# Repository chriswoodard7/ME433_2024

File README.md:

# ME433_2024
Repo for ME 433 assignments during the Spring 2024 quarter

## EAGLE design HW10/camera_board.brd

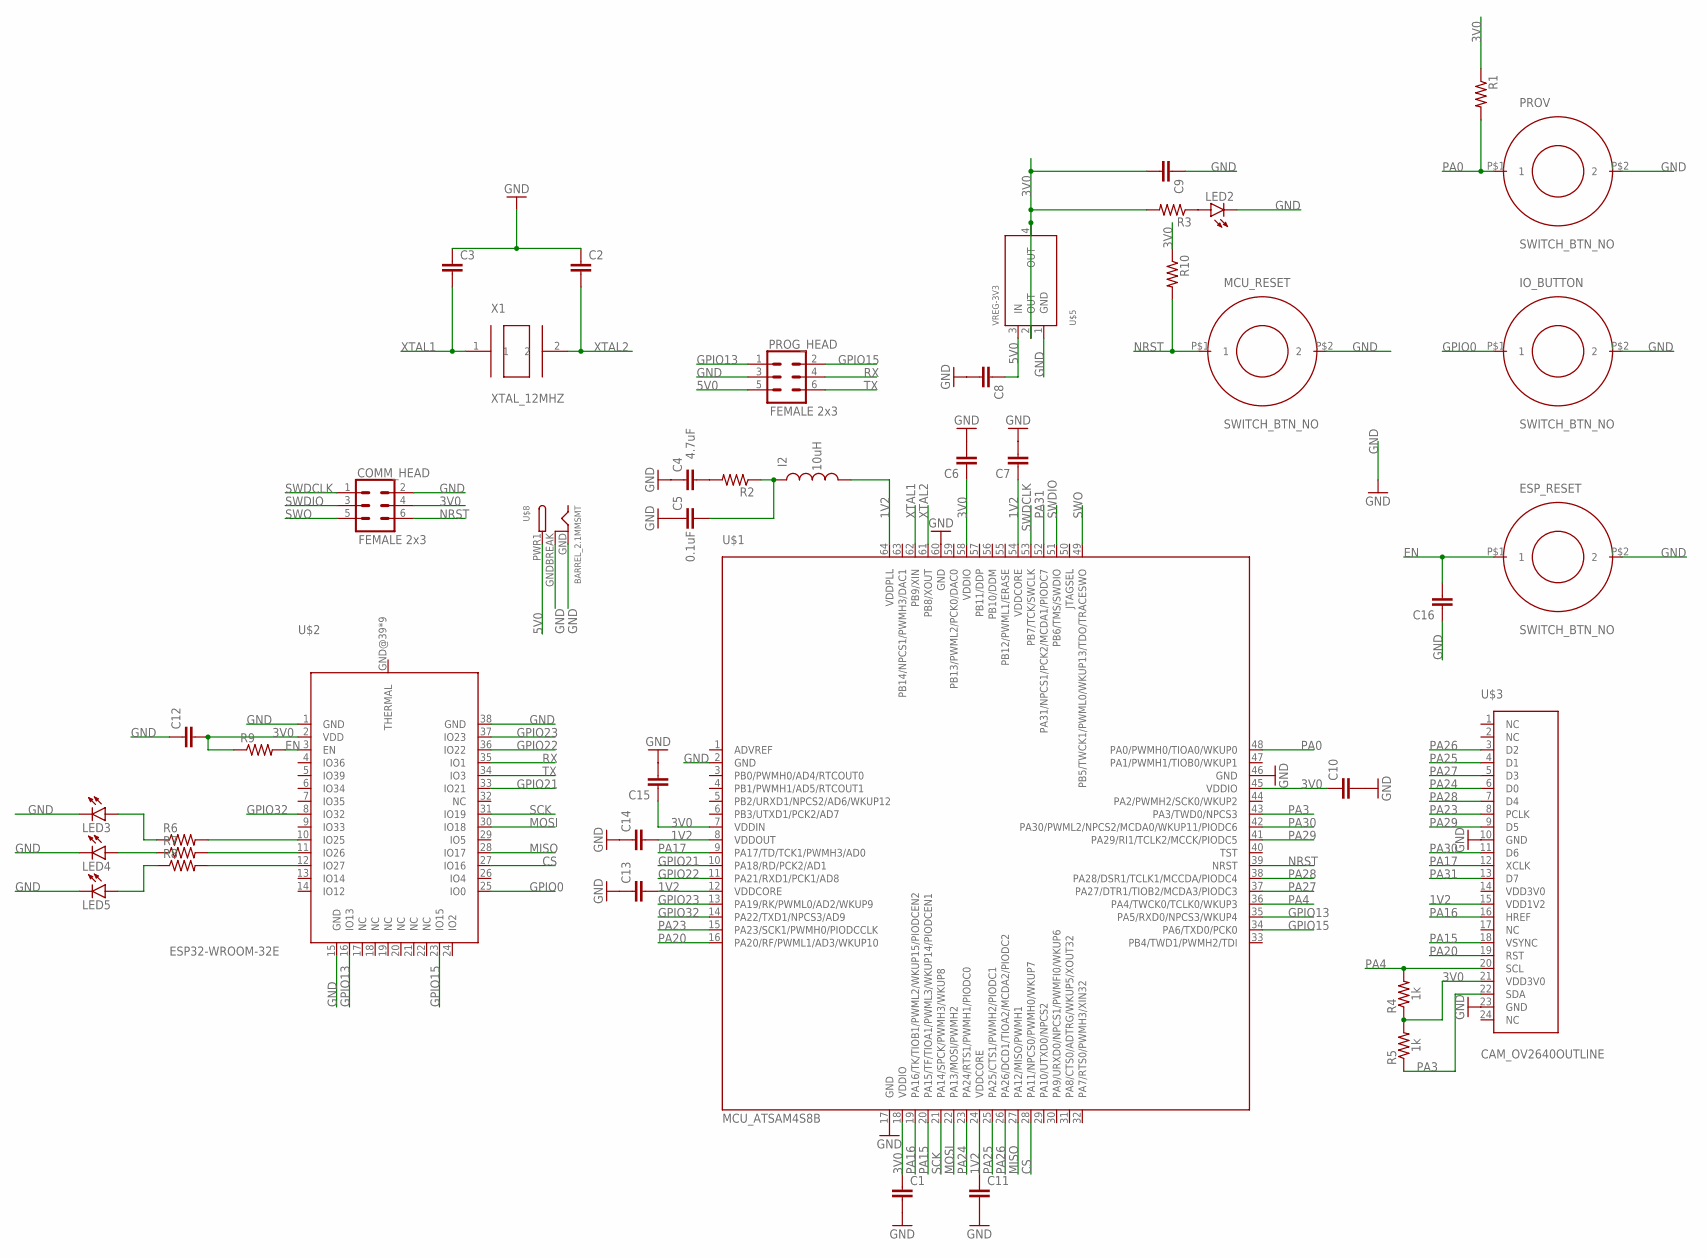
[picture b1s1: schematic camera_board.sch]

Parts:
C1, C2, C3, C6, C7, C8, C9, C10, C11, C12, C13, C14, C15, C16: CAP; 0805
C4: 4.7uF; 0805
C5: 0.1uF; 0805
COMM_HEAD: FEMALE 2x3; 2X3
ESP_RESET: SWITCH_BTN_NO; BTN_2
I2: 10uH; 0805
IO_BUTTON: SWITCH_BTN_NO; BTN_2
LED2, LED3, LED4, LED5: LED0603; LED-0603
MCU_RESET: SWITCH_BTN_NO; BTN_2
PROG_HEAD: FEMALE 2x3; 2X3
PROV: SWITCH_BTN_NO; BTN_2
R1, R2, R3, R6, R7, R8, R9, R10: RES; 0805
R4, R5: 1k; 0805
U$1: MCU_ATSAM4S8B; QFP50P1200X1200X160-64N
U$2: ESP32-WROOM-32E
U$3: CAM_OV2640OUTLINE; CAM_CONN
U$5: VREG-3V3; R-PDSO-G4_TI
U$8: BARREL_2.1MMSMT; DCJACK_2MM_SMT
X1: XTAL_12MHZ; ABM7-16.000MHZ-D2Y-T

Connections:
1V2: C7.1, C11.1, C13.2, C14.2, I2.2, U$1.8 (VDDOUT), U$1.12 (VDDCORE), U$1.24 (VDDCORE), U$1.54 (VDDCORE), U$1.64 (VDDPLL), U$3.15 (VDD1V2)
3V0: C1.1, C6.1, C9.2, C10.1, C12.2, C15.1, COMM_HEAD.4, R1.1, R3.2, R4.1, R5.2, R9.1, R10.1, U$1.7 (VDDIN), U$1.18 (VDDIO), U$1.45 (VDDIO), U$1.58 (VDDIO), U$2.2 (VDD), U$3.21 (VDD3V0), U$5.2 (OUT), U$5.4 (OUT)
5V0: C8.1, PROG_HEAD.5, U$5.3 (IN), U$8.PWR1 (PWR)
CS: U$1.28 (PA11/NPCS0/PWMH0/WKUP7), U$2.27 (IO16)
EN: C16.2, ESP_RESET.P$1 (1), R9.2, U$2.3 (EN)
GND: C1.2, C2.1, C3.1, C4.1, C5.1, C6.2, C7.2, C8.2, C9.1, C10.2, C11.2, C12.1, C13.1, C14.1, C15.2, C16.1, COMM_HEAD.2, ESP_RESET.P$2 (2), IO_BUTTON.P$2 (2), LED2.C, LED3.C, LED4.C, LED5.C, MCU_RESET.P$2 (2), PROG_HEAD.3, PROV.P$2 (2), U$1.2 (GND), U$1.17 (GND), U$1.46 (GND), U$1.60 (GND), U$2.1 (GND), U$2.15 (GND), U$2.38 (GND), U$3.10 (GND), U$3.23 (GND), U$5.1 (GND), U$8.GND, U$8.GNDBREAK
GPIO0: IO_BUTTON.P$1 (1), U$2.25 (IO0)
GPIO13: PROG_HEAD.1, U$1.35 (PA5/RXD0/NPCS3/WKUP4), U$2.16 (IO13)
GPIO15: PROG_HEAD.2, U$1.34 (PA6/TXD0/PCK0), U$2.23 (IO15)
GPIO21: U$1.10 (PA18/RD/PCK2/AD1), U$2.33 (IO21)
GPIO22: U$1.11 (PA21/RXD1/PCK1/AD8), U$2.36 (IO22)
GPIO23: U$1.13 (PA19/RK/PWML0/AD2/WKUP9), U$2.37 (IO23)
GPIO32: U$1.14 (PA22/TXD1/NPCS3/AD9), U$2.8 (IO32)
MISO: U$1.27 (PA12/MISO/PWMH1), U$2.28 (IO17)
MOSI: U$1.22 (PA13/MOSI/PWMH2), U$2.30 (IO18)
unnamed: C5.2, I2.1, R2.1
unnamed: C4.2, R2.2
unnamed: LED2.A, R3.1
unnamed: LED3.A, R6.1
unnamed: R6.2, U$2.10 (IO25)
unnamed: R7.2, U$2.11 (IO26)
unnamed: R8.2, U$2.12 (IO27)
unnamed: LED4.A, R7.1
unnamed: LED5.A, R8.1
NRST: COMM_HEAD.6, MCU_RESET.P$1 (1), R10.2, U$1.39 (NRST)
PA0: PROV.P$1 (1), R1.2, U$1.48 (PA0/PWMH0/TIOA0/WKUP0)
PA3: R5.1, U$1.43 (PA3/TWD0/NPCS3), U$3.22 (SDA)
PA4: R4.2, U$1.36 (PA4/TWCK0/TCLK0/WKUP3), U$3.20 (SCL)
PA15: U$1.20 (PA15/TF/TIOA1/PWML3/WKUP14/PIODCEN1), U$3.18 (VSYNC)
PA16: U$1.19 (PA16/TK/TIOB1/PWML2/WKUP15/PIODCEN2), U$3.16 (HREF)
PA17: U$1.9 (PA17/TD/TCK1/PWMH3/AD0), U$3.12 (XCLK)
PA20: U$1.16 (PA20/RF/PWML1/AD3/WKUP10), U$3.19 (RST)
PA23: U$1.15 (PA23/SCK1/PWMH0/PIODCCLK), U$3.8 (PCLK)
PA24: U$1.23 (PA24/RTS1/PWMH1/PIODC0), U$3.6 (D0)
PA25: U$1.25 (PA25/CTS1/PWMH2/PIODC1), U$3.4 (D1)
PA26: U$1.26 (PA26/DCD1/TIOA2/MCDA2/PIODC2), U$3.3 (D2)
PA27: U$1.37 (PA27/DTR1/TIOB2/MCDA3/PIODC3), U$3.5 (D3)
PA28: U$1.38 (PA28/DSR1/TCLK1/MCCDA/PIODC4), U$3.7 (D4)
PA29: U$1.41 (PA29/RI1/TCLK2/MCCK/PIODC5), U$3.9 (D5)
PA30: U$1.42 (PA30/PWML2/NPCS2/MCDA0/WKUP11/PIODC6), U$3.11 (D6)
PA31: U$1.52 (PA31/NPCS1/PCK2/MCDA1/PIODC7), U$3.13 (D7)
RX: PROG_HEAD.4, U$2.35 (IO1)
SCK: U$1.21 (PA14/SPCK/PWMH3/WKUP8), U$2.31 (IO19)
SWDCLK: COMM_HEAD.1, U$1.53 (PB7/TCK/SWCLK)
SWDIO: COMM_HEAD.3, U$1.51 (PB6/TMS/SWDIO)
SWO: COMM_HEAD.5, U$1.49 (PB5/TWCK1/PWML0/WKUP13/TDO/TRACESWO)
TX: PROG_HEAD.6, U$2.34 (IO3)
XTAL1: C3.2, U$1.62 (PB9/XIN), X1.1
XTAL2: C2.2, U$1.61 (PB8/XOUT), X1.2

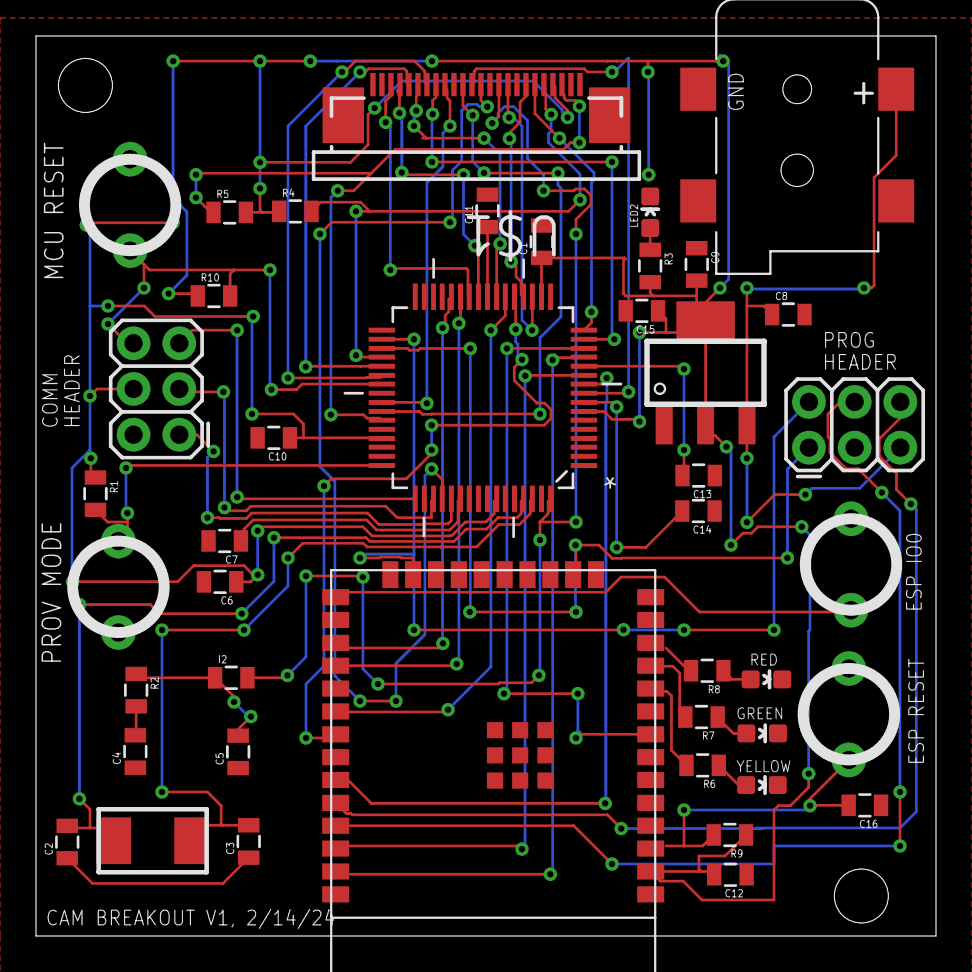
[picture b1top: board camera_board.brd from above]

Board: 2 copper layers, 50.0 x 50.0 mm, 43 parts (0 on the bottom side), 49 nets.

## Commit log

2024-04-04 hw2 commit 3:20pm 4/4
2024-04-06 commit 8:19pm 4/5
2024-04-18 made text file
2024-04-18 branch test
2024-05-17 hw14 commit
2024-05-26 HW15 commit
2024-05-30 final hw11 commit
2024-06-03 hw10 commit

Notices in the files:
parts and their libraries:
SparkFun-Connectors: Licensing: Creative Commons ShareAlike 4.0 International - https://creativecommons.org/licenses/by-sa/4.0
